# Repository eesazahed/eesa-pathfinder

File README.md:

# eesa-pathfinder

my first PCB (that actually works)

buttons 1, 2, and 3 each light up their corresponding LED. button 4 activates a wave-like pattern across the led board momentarily.

<br />

<br />

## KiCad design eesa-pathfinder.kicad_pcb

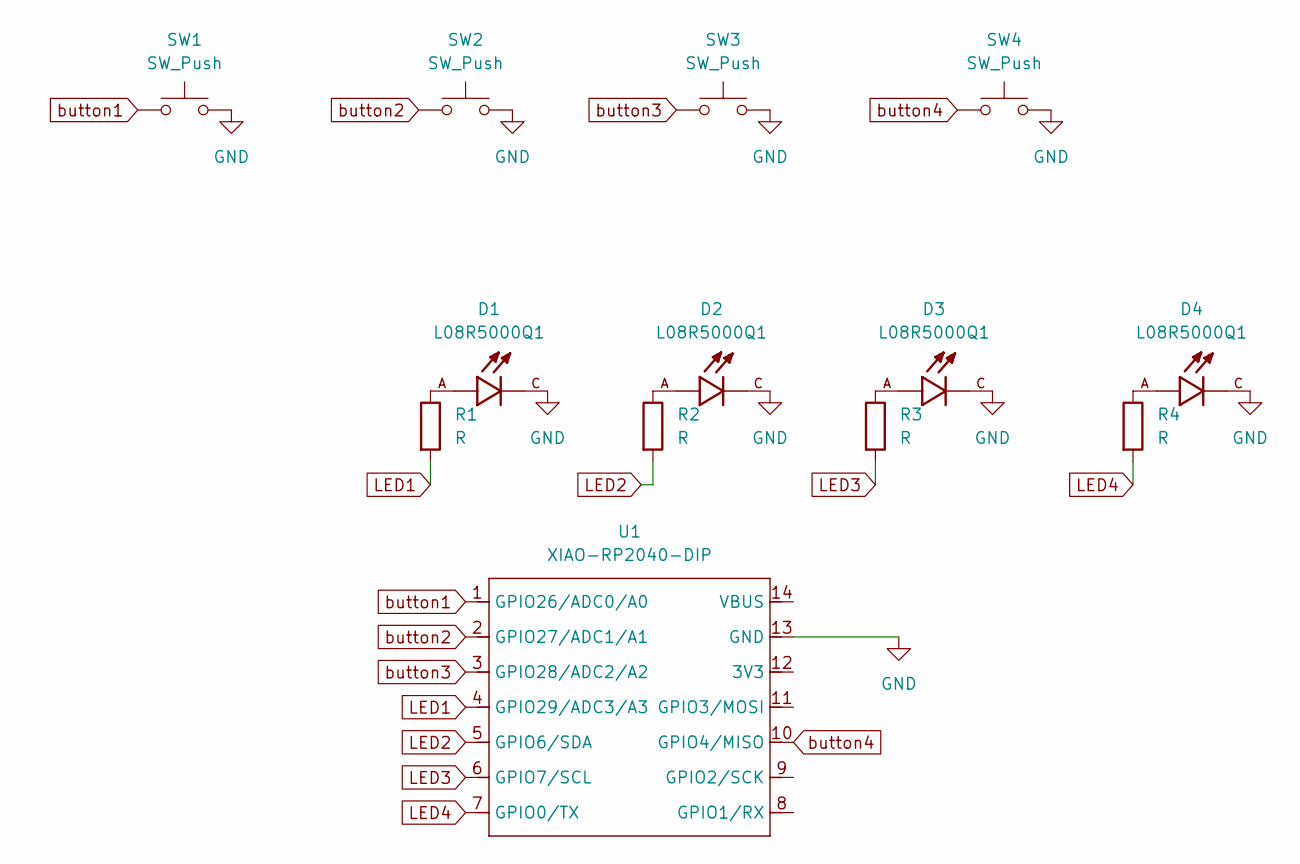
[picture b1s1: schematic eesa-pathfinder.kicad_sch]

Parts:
D1, D2, D3, D4: L08R5000Q1; LEDRD254W57D500H1070; PARTREV NA
R1, R2, R3, R4: R; R_Axial_DIN0204_L3.6mm_D1.6mm_P5.08mm_Horizontal
SW1, SW2, SW3, SW4: SW_Push; SW_Cherry_MX_1.00u_PCB
U1: XIAO-RP2040-DIP

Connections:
GND: D1.C, D2.C, D3.C, D4.C, SW1.2, SW2.2, SW3.2, SW4.2, U1.13 (GND)
LED1: R1.2, U1.4 (GPIO29/ADC3/A3)
LED2: R2.2, U1.5 (GPIO6/SDA)
LED3: R3.2, U1.6 (GPIO7/SCL)
LED4: R4.2, U1.7 (GPIO0/TX)
unnamed: D1.A, R1.1
unnamed: D2.A, R2.1
unnamed: D3.A, R3.1
unnamed: D4.A, R4.1
button1: SW1.1, U1.1 (GPIO26/ADC0/A0)
button2: SW2.1, U1.2 (GPIO27/ADC1/A1)
button3: SW3.1, U1.3 (GPIO28/ADC2/A2)
button4: SW4.1, U1.10 (GPIO4/MISO)

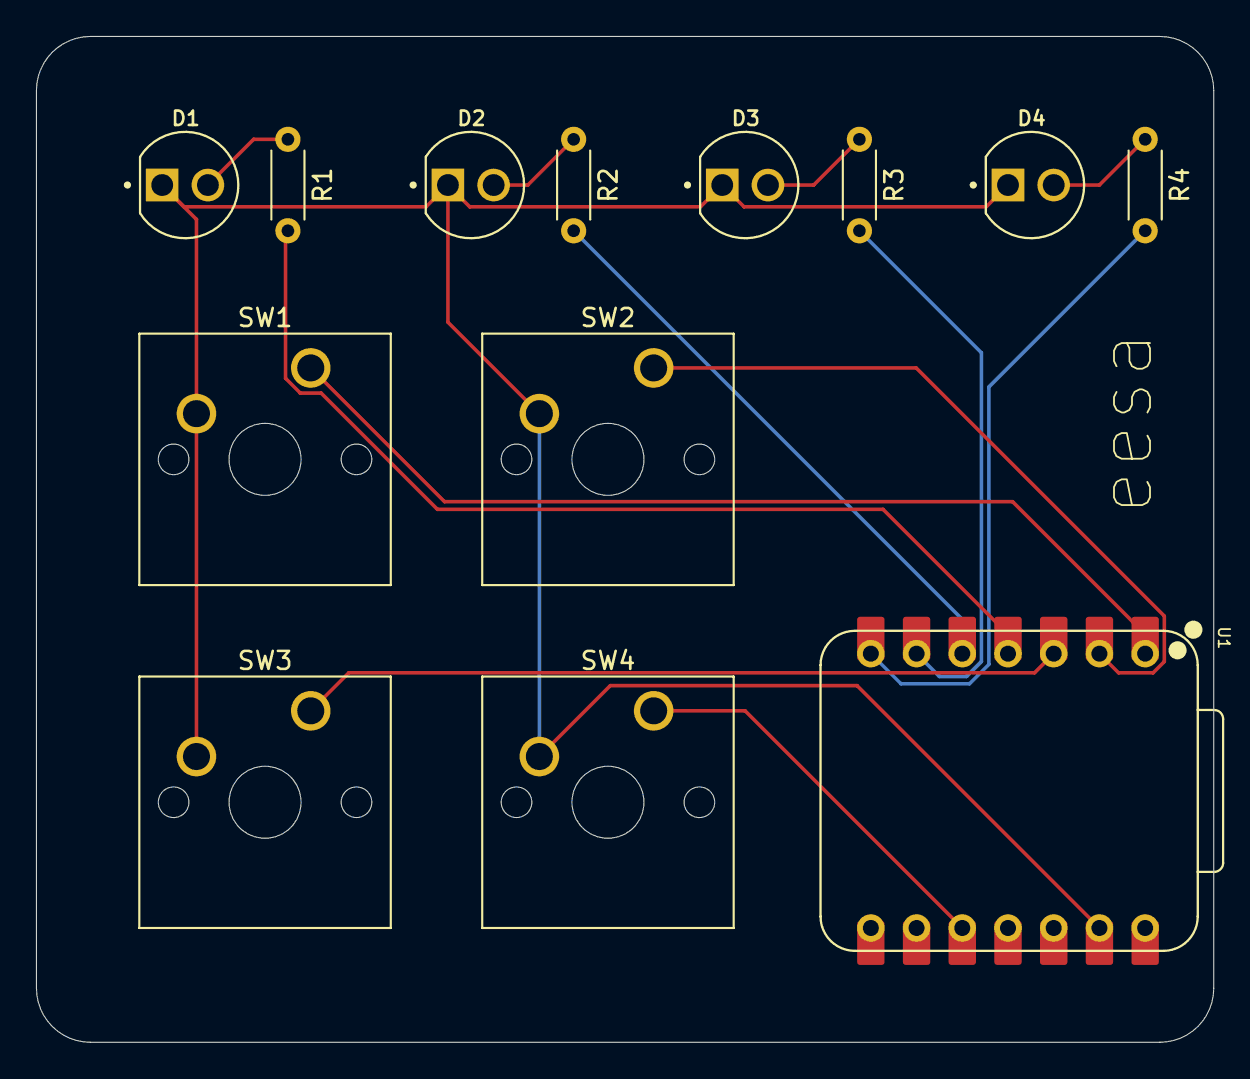
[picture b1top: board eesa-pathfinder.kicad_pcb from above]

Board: 2 copper layers, 65.4 x 55.9 mm, 13 parts (0 on the bottom side), 13 nets.

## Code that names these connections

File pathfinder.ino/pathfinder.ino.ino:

int BUT1 = D0;
int BUT2 = D1;
int BUT3 = D2;
int BUT4 = D7;

int LED1 = D3;
int LED2 = D4;
int LED3 = D5;
int LED4 = D6;

unsigned long pressStart = 0;
bool longPressActive = false;

void setup() {
  pinMode(BUT1, INPUT_PULLUP);
  pinMode(BUT2, INPUT_PULLUP);
  pinMode(BUT3, INPUT_PULLUP);
  pinMode(BUT4, INPUT_PULLUP);

  pinMode(LED1, OUTPUT);
  pinMode(LED2, OUTPUT);
  pinMode(LED3, OUTPUT);
  pinMode(LED4, OUTPUT);
}

void loop() {
  digitalWrite(LED1, digitalRead(BUT1) == LOW ? HIGH : LOW);
  digitalWrite(LED2, digitalRead(BUT2) == LOW ? HIGH : LOW);
  digitalWrite(LED3, digitalRead(BUT3) == LOW ? HIGH : LOW);

  if (digitalRead(BUT4) == LOW && pressStart == 0) {
    pressStart = millis();
  }
  if (digitalRead(BUT4) == HIGH && pressStart != 0) {
    unsigned long pressDuration = millis() - pressStart;
    pressStart = 0;
    if (pressDuration > 2000 && !longPressActive) {
      longPressActive = true;
      patternMode();
      longPressActive = false;
    }
  }
}

void patternMode() {
  digitalWrite(LED1, LOW);
  digitalWrite(LED2, LOW);
  digitalWrite(LED3, LOW);
  digitalWrite(LED4, LOW);
  delay(300);

  for (int i = 0; i < 3; i++) {
    digitalWrite(LED1, HIGH); delay(150);
    digitalWrite(LED1, LOW);  delay(50);
    digitalWrite(LED2, HIGH); delay(150);
    digitalWrite(LED2, LOW);  delay(50);
    digitalWrite(LED3, HIGH); delay(150);
    digitalWrite(LED3, LOW);  delay(50);
    digitalWrite(LED4, HIGH); delay(150);
    digitalWrite(LED4, LOW);  delay(50);

    digitalWrite(LED3, HIGH); delay(150);
    digitalWrite(LED3, LOW);  delay(50);
    digitalWrite(LED2, HIGH); delay(150);
    digitalWrite(LED2, LOW);  delay(50);
    digitalWrite(LED1, HIGH); delay(150);
    digitalWrite(LED1, LOW);  delay(50);
  }

  digitalWrite(LED1, LOW);
  digitalWrite(LED2, LOW);
  digitalWrite(LED3, LOW);
  digitalWrite(LED4, LOW);
}

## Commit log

2025-07-28 add files
2025-07-28 add dril files and gerber
2025-07-28 add gerber stuff
